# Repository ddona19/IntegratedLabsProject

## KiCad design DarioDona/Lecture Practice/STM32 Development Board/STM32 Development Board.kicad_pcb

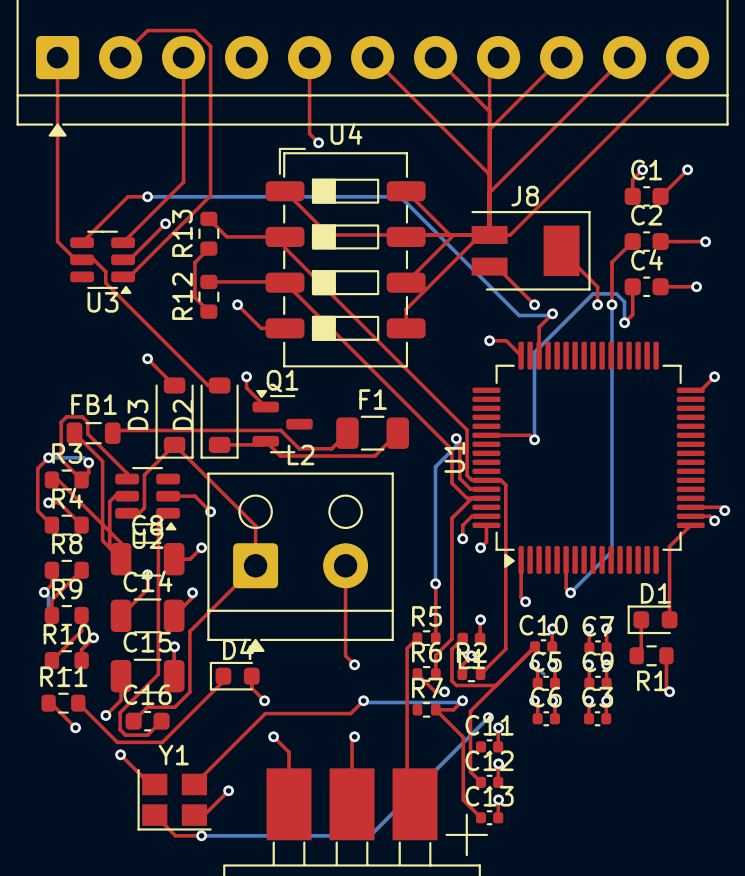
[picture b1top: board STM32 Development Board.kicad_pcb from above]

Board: 4 copper layers, 46 parts (0 on the bottom side), 28 nets.

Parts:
C1: 4u7; C_0603_1608Metric
C2, C4: 2u2; C_0603_1608Metric
C3, C5, C6, C7, C9: 100n; C_0402_1005Metric
C8, C14, C15: 10u; C_1206_3216Metric
C10: 1u; C_0402_1005Metric
C11, C13: 12p; C_0402_1005Metric
C12: 10n; C_0402_1005Metric
C16: 10n; C_0603_1608Metric
D1: BLUE; LED_0603_1608Metric
D2, D3: B5819W; D_SOD-123
D4: RED; LED_0603_1608Metric
F1: 250mA; Fuse_1206_3216Metric
FB1: 600 @ 600MHz; L_0805_2012Metric
J2: 10118193-0001LF; TerminalBlock_4Ucon_1x11_P3.50mm_Horizontal
J8: DC-005; D_SMB_Modified
L1: 39n; L_0402_1005Metric
L2: 10u; TerminalBlock_RND_205-00001_1x02_P5.00mm_Horizontal
Q1: AO3401A; SOT-23
R1: 1k5; R_0603_1608Metric
R2, R6: 2k2; R_0402_1005Metric
R3: 100k; R_0603_1608Metric
R4: 68k; R_0603_1608Metric
R5: 10k; R_0402_1005Metric
R7: 47; R_0402_1005Metric
R8: 47k; R_0603_1608Metric
R9: 15k; R_0603_1608Metric
R10: 270; R_0603_1608Metric
R11: 1k; R_0603_1608Metric
R12, R13: 2k2; R_0603_1608Metric
U1: STM32F405RGT6; LQFP-64_10x10mm_P0.5mm
U2: MP2359DJ-LF-Z; SOT-23-6
U3: USBLC6-2SC6; SOT-23-6
U4: MAX30101EFD; SW_DIP_SPSTx04_Slide_6.7x11.72mm_W6.73mm_P2.54mm_LowProfile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
U5: PCM12SMTR; CP_Elec_CAP-XX_DMF3Zxxxxxxxx3D
Y1: 16MHz; Crystal_SMD_3225-4Pin_3.2x2.5mm

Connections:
+3.3V: C1.1, C3.1, C5.1, C6.1, C7.1, C9.1, C14.1, C15.1, D4.2 (A), L1.1, L2.2, R2.1, R6.1, R8.1, U1.1 (VBAT), U1.19 (VDD), U1.32 (VDD), U1.48 (VDD), U1.64 (VDD), U5.3
+3.3VA: C10.1, C12.1, L1.2, U1.13 (VDDA)
+5V: D2.2 (A), J2.1 (VUSB), U3.5 (VBUS)
BOOT0: R5.2, U1.60 (BOOT0)
BUCK_BST: C16.2, U2.1 (BST)
BUCK_EN: R3.2, R4.1, U2.4 (EN)
BUCK_FB: R8.2, R9.1, U2.3 (FB)
BUCK_IN: C8.1, FB1.1, R3.1, U2.5 (IN)
BUCK_SW: C16.1, D3.1 (K), L2.1, U2.6 (SW)
GND: C1.2, C2.2, C3.2, C4.2, C5.2, C6.2, C7.2, C8.2, C9.2, C10.2, C11.2, C12.2, C13.2, C14.2, C15.2, D3.2 (A), J2.5 (GND), J8.2, J8.3, Q1.1 (G), R1.1, R4.2, R10.2, R11.1, U1.12 (VSSA), U1.18 (VSS), U1.63 (VSS), U2.2 (GND), U3.2 (GND), U4.4 (PGND), U5.2, Y1.2, Y1.4
HSE_IN: C11.1, U1.24 (PC4), Y1.1
HSE_OUT: R7.1, U1.25 (PC5)
I2C1_SCL: R2.2, R13.2, U1.59 (PB7), U4.2 (SCL)
I2C1_SDA: R6.2, R12.2, U1.61 (PB8), U4.3 (SDA)
LED_STATUS: D1.2 (A), U1.17 (PA3)
unnamed: C13.1, R7.2, Y1.3
unnamed: D1.1 (K), R1.2
unnamed: D2.1 (K), F1.2, Q1.2 (S)
unnamed: D4.1 (K), R11.2
unnamed: F1.1, FB1.2
unnamed: R5.1, U5.1
unnamed: R9.2, R10.1
unnamed: C4.1, U1.54 (PD2)
unnamed: C2.1, U1.6 (PH1)
unnamed: R12.1, R13.1
USB_CONN_D_N: J2.2 (D-), U3.1 (I/O1)
USB_CONN_D_P: J2.3 (D+), U3.3 (I/O2)
USB_D_P: U1.46 (PA13), U3.4 (I/O2)

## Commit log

2025-06-12 Dario Dona project
    Dario Dona project for integrated labs
